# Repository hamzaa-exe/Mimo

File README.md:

# Mimo

Mimo is a cute DIY desktop robot built around the Seeed Studio XIAO ESP32-S3. It combines a custom PCB, a 3D-printed enclosure, an OLED display, touch interaction, Wi-Fi, and audio to create a small interactive desktop companion.

Mimo normally displays cute animated eyes and different emotions. The user can interact with Mimo by touching the TTP223 sensor, which cycles through different modes such as time, weather, and the normal animation mode.

## Features

- Cute animated eyes and different emotions
- 2.42" SSD1309 OLED display
- TTP223 touch sensor for interaction
- Wi-Fi connectivity
- Online weather information
- Real-time clock display
- MAX98357A I2S audio amplifier
- Speaker for sounds and future voice playback
- Li-Po battery powered
- Physical ON/OFF switch
- Custom PCB designed in KiCad
- Custom 3D-printed enclosure designed in Fusion 360

## How It Works

Mimo starts in its normal animation mode, where the OLED continuously displays different eye expressions and emotions.

The TTP223 touch sensor is used to change between modes:

    First Touch  ->  Time
    Second Touch ->  Weather
    Third Touch  ->  Back to Animations

The ESP32-S3 connects to Wi-Fi and retrieves weather information from an online API. The MAX98357A amplifier is used to drive the speaker, allowing Mimo to produce sounds and eventually play recorded voice clips.

## Hardware

| Component | Purpose |
|-----------|---------|
| XIAO ESP32-S3 | Main microcontroller |
| 2.42" SSD1309 OLED | Eyes, animations and information |
| TTP223 | Touch interaction |
| MAX98357A | I2S audio amplifier |
| Speaker | Sounds and voice |
| Li-Po Battery | Power source |
| Physical Switch | Power ON/OFF |
| Custom PCB | Main electronics board |

## Software

The firmware is being developed using Arduino IDE and C++.

Main libraries and technologies used:

- ESP32 Arduino Core
- U8g2
- ArduinoJson
- Wi-Fi
- HTTP requests
- I2S audio
- Online weather API

## Project Structure

    Mimo/
    ├── firmware/
    │   └── mimo.ino
    ├── pcb/
    │   └── KiCad/
    ├── case/
    │   └── Fusion360/
    ├── README.md
    └── LICENSE

## PCB

The Mimo PCB was designed from scratch in KiCad. It connects the XIAO ESP32-S3 with the OLED, touch sensor, audio amplifier, power system and other components.

The PCB is designed to fit inside the custom 3D-printed robot enclosure.

## Enclosure

The enclosure was designed in Fusion 360 specifically for Mimo's electronics. It includes mounting points for the PCB, openings for the OLED, USB connection, power switch and speaker, along with external horns to give Mimo its recognizable appearance.

## Future Plans

- Add more eye animations and emotions
- Add more touch interactions
- Improve weather animations
- Add battery status
- Add more sound effects
- Add sleep and wake animations
- Add additional interactive features

## Project Status

This project is being built as a complete DIY robot from the electronics and PCB design to the firmware and 3D-printed enclosure.

## License

This project is open source. See the LICENSE file for details.

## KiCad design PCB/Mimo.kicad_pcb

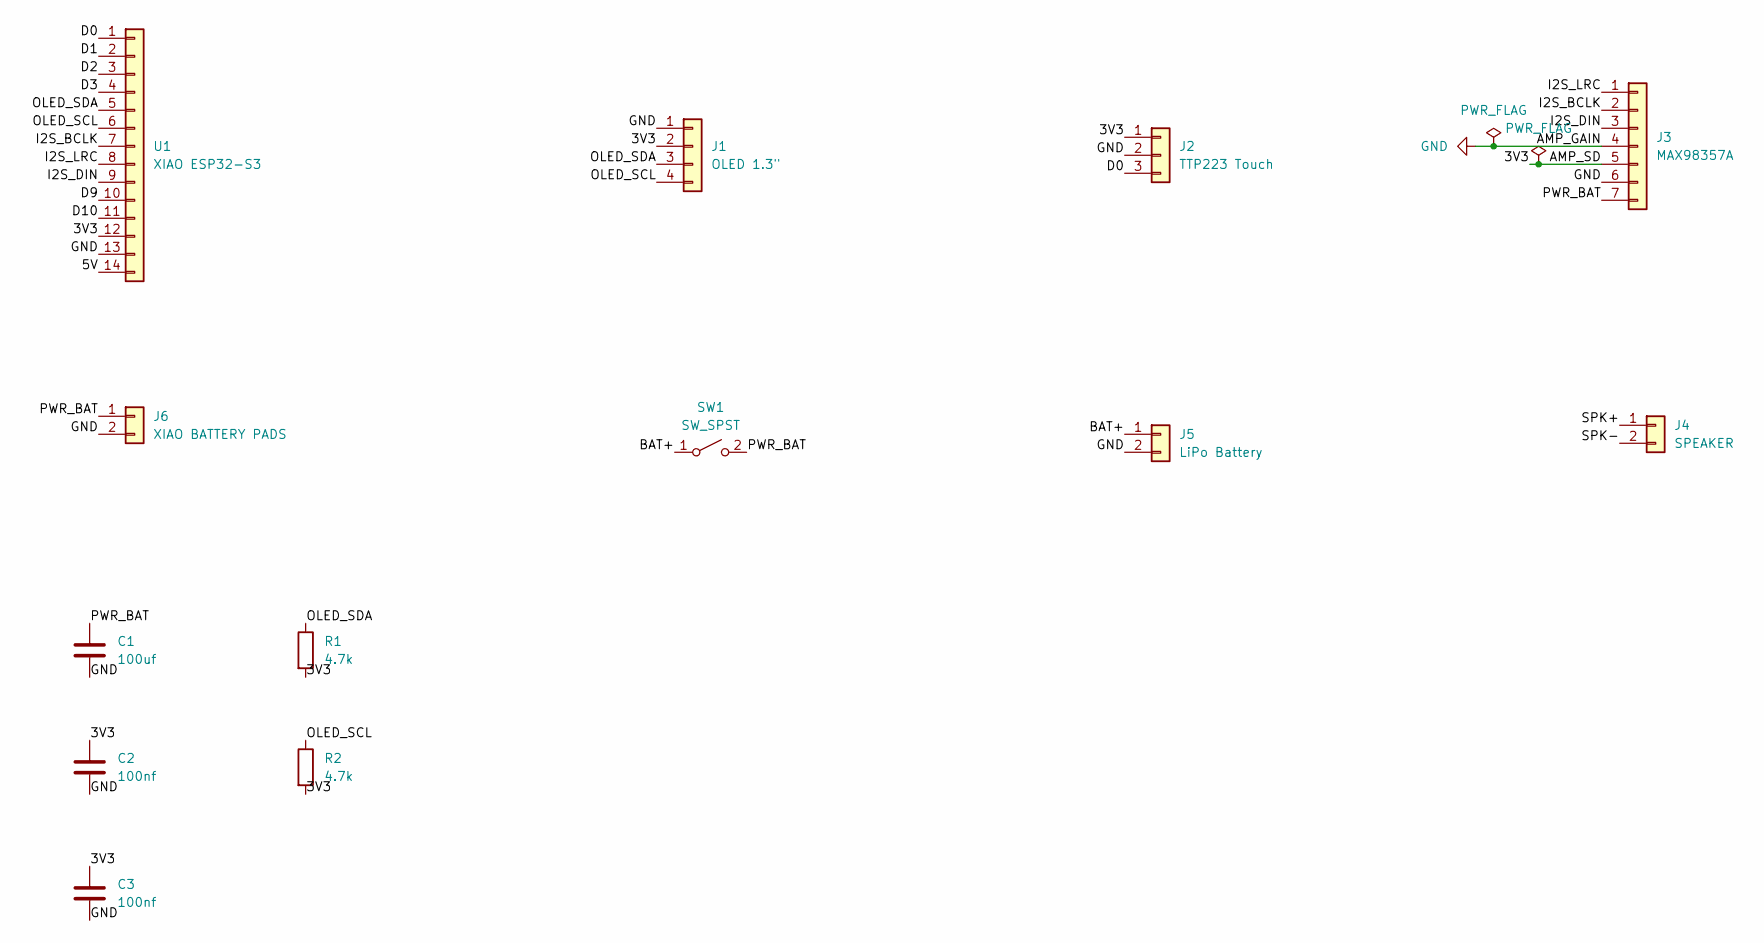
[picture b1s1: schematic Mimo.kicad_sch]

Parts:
C1: 100uf; CP_Radial_D6.3mm_P2.50mm
C2, C3: 100nf; C_0805_2012Metric
J1: OLED 1.3"; JST_PH_B4B-PH-K_1x04_P2.00mm_Vertical
J2: TTP223 Touch; JST_PH_B3B-PH-K_1x03_P2.00mm_Vertical
J3: MAX98357A; PinHeader_1x07_P2.54mm_Vertical
J4: SPEAKER; JST_PH_B2B-PH-K_1x02_P2.00mm_Vertical
J5: LiPo Battery; JST_PH_B2B-PH-K_1x02_P2.00mm_Vertical
J6: XIAO BATTERY PADS; JST_PH_B2B-PH-K_1x02_P2.00mm_Vertical
R1, R2: 4.7k; R_0805_2012Metric
SW1: SW_SPST; SW_SPDT_PCM12
U1: XIAO ESP32-S3; XIAO-ESP32-S3-DIP

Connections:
/3V3: C2.1, C3.1, J1.2, J2.1, J3.5, R1.2, R2.2, U1.12
/5V: U1.14
/BAT+: J5.1, SW1.1 (A)
/D0: J2.3, U1.1
/D1: U1.2
/D2: U1.3
/D3: U1.4
/D9: U1.10
/D10: U1.11
/I2S_BCLK: J3.2, U1.7
/I2S_DIN: J3.3, U1.9
/I2S_LRC: J3.1, U1.8
/OLED_SCL: J1.4, R2.1, U1.6
/OLED_SDA: J1.3, R1.1, U1.5
/PWR_BAT: C1.1, J3.7, J6.1, SW1.2 (B)
/SPK+: J4.1
/SPK-: J4.2
GND: C1.2, C2.2, C3.2, J1.1, J2.2, J3.4, J3.6, J5.2, J6.2, U1.13

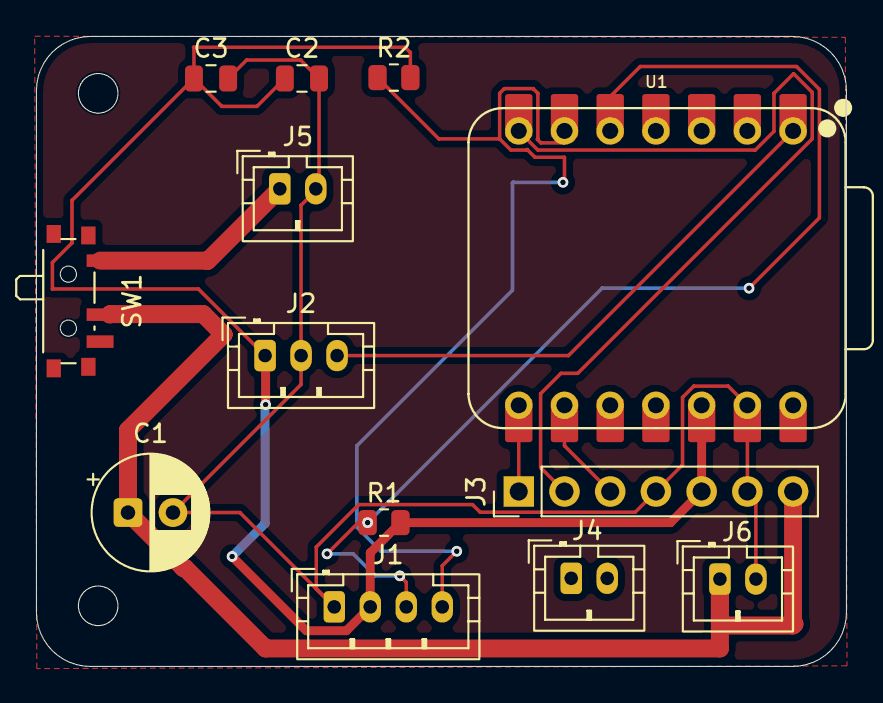
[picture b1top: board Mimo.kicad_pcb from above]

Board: 2 copper layers, 45.0 x 35.0 mm, 13 parts (0 on the bottom side), 10 nets.

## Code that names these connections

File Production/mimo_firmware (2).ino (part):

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// ========================================================

// OLED
#define OLED_SDA_PIN 5     // XIAO D4
#define OLED_SCL_PIN 6     // XIAO D5

// Touch
#define TOUCH_PIN 1        // XIAO D0 = GPIO1

// MAX98357A I2S
// Change these three if your physical wiring is different.
#define I2S_BCLK_PIN 43    // XIAO D6
#define I2S_LRC_PIN  44    // XIAO D7
#define I2S_DIN_PIN   7    // XIAO D8


// ========================================================
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
    .gpio_cfg = {
      .mclk = I2S_GPIO_UNUSED,
      .bclk = (gpio_num_t)I2S_BCLK_PIN,
      .ws   = (gpio_num_t)I2S_LRC_PIN,
      .dout = (gpio_num_t)I2S_DIN_PIN,
      .din  = I2S_GPIO_UNUSED
    }
  };
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
  // OLED
  Wire.begin(
    OLED_SDA_PIN,
    OLED_SCL_PIN
  );

  oled.begin();
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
